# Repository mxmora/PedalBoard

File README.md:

# PedalBoard
	
	Board for multiple button controller

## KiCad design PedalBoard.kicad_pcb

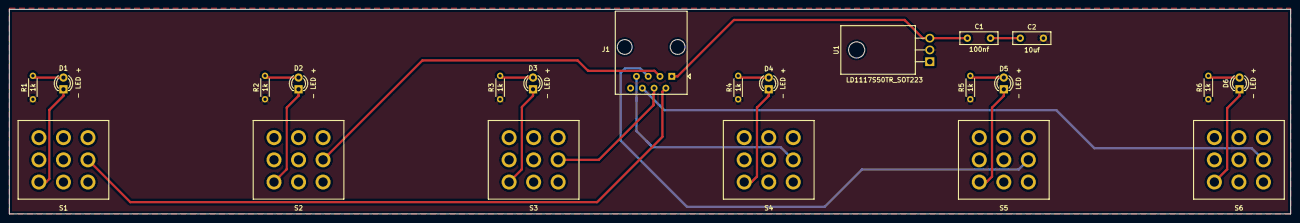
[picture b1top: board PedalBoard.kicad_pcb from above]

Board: 2 copper layers, 276.9 x 44.2 mm, 22 parts (0 on the bottom side), 22 nets.

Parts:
C1: 100nf; C_Disc_D8.0mm_W2.5mm_P5.00mm
C2: 10uf; C_Disc_D8.0mm_W2.5mm_P5.00mm
D1, D2, D3, D4, D5, D6: - LED +; LED_D3.0mm
J1: 8P8C; RJ45_Amphenol_54602-x08_Horizontal
R1, R2, R3, R4, R5, R6: 1k; R_Axial_DIN0204_L3.6mm_D1.6mm_P5.08mm_Horizontal
S1, S2, S3, S4, S5, S6: SF17020F-0302-21R-L-015; Footswitch_3PDT
U1: LD1117S50TR_SOT223; TO-220F-3_Horizontal_TabDown

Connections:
+9V: C1.1, J1.1, U1.3
GND: J1.8, S1.3, S1.8, S2.3, S2.8, S3.3, S3.8, S4.3, S4.8, S5.3, S5.8, S6.3, S6.8, U1.1
unnamed: C1.2, C2.2
unnamed: D1.1, S1.7
unnamed: D1.2, R1.2
unnamed: D2.1, S2.7
unnamed: D2.2, R2.2
unnamed: D3.1, S3.7
unnamed: D3.2, R3.2
unnamed: D4.1, S4.7
unnamed: D4.2, R4.2
unnamed: D5.1, S5.7
unnamed: D5.2, R5.2
unnamed: D6.1, S6.7
unnamed: D6.2, R6.2
unnamed: J1.2, S1.2
unnamed: J1.3, S2.2
unnamed: J1.4, S3.2
unnamed: J1.5, S5.2
unnamed: J1.6, S6.2
unnamed: J1.7, S4.2
REG_5v: C2.1, R1.1, R2.1, R3.1, R4.1, R5.1, R6.1, U1.2

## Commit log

2019-05-19 inital check in
2019-05-19 layout board
2019-05-19 add regulator
2019-05-23 Update footswitch library
